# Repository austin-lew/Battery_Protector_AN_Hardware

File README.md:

# Battery_Protector_AN_Hardware

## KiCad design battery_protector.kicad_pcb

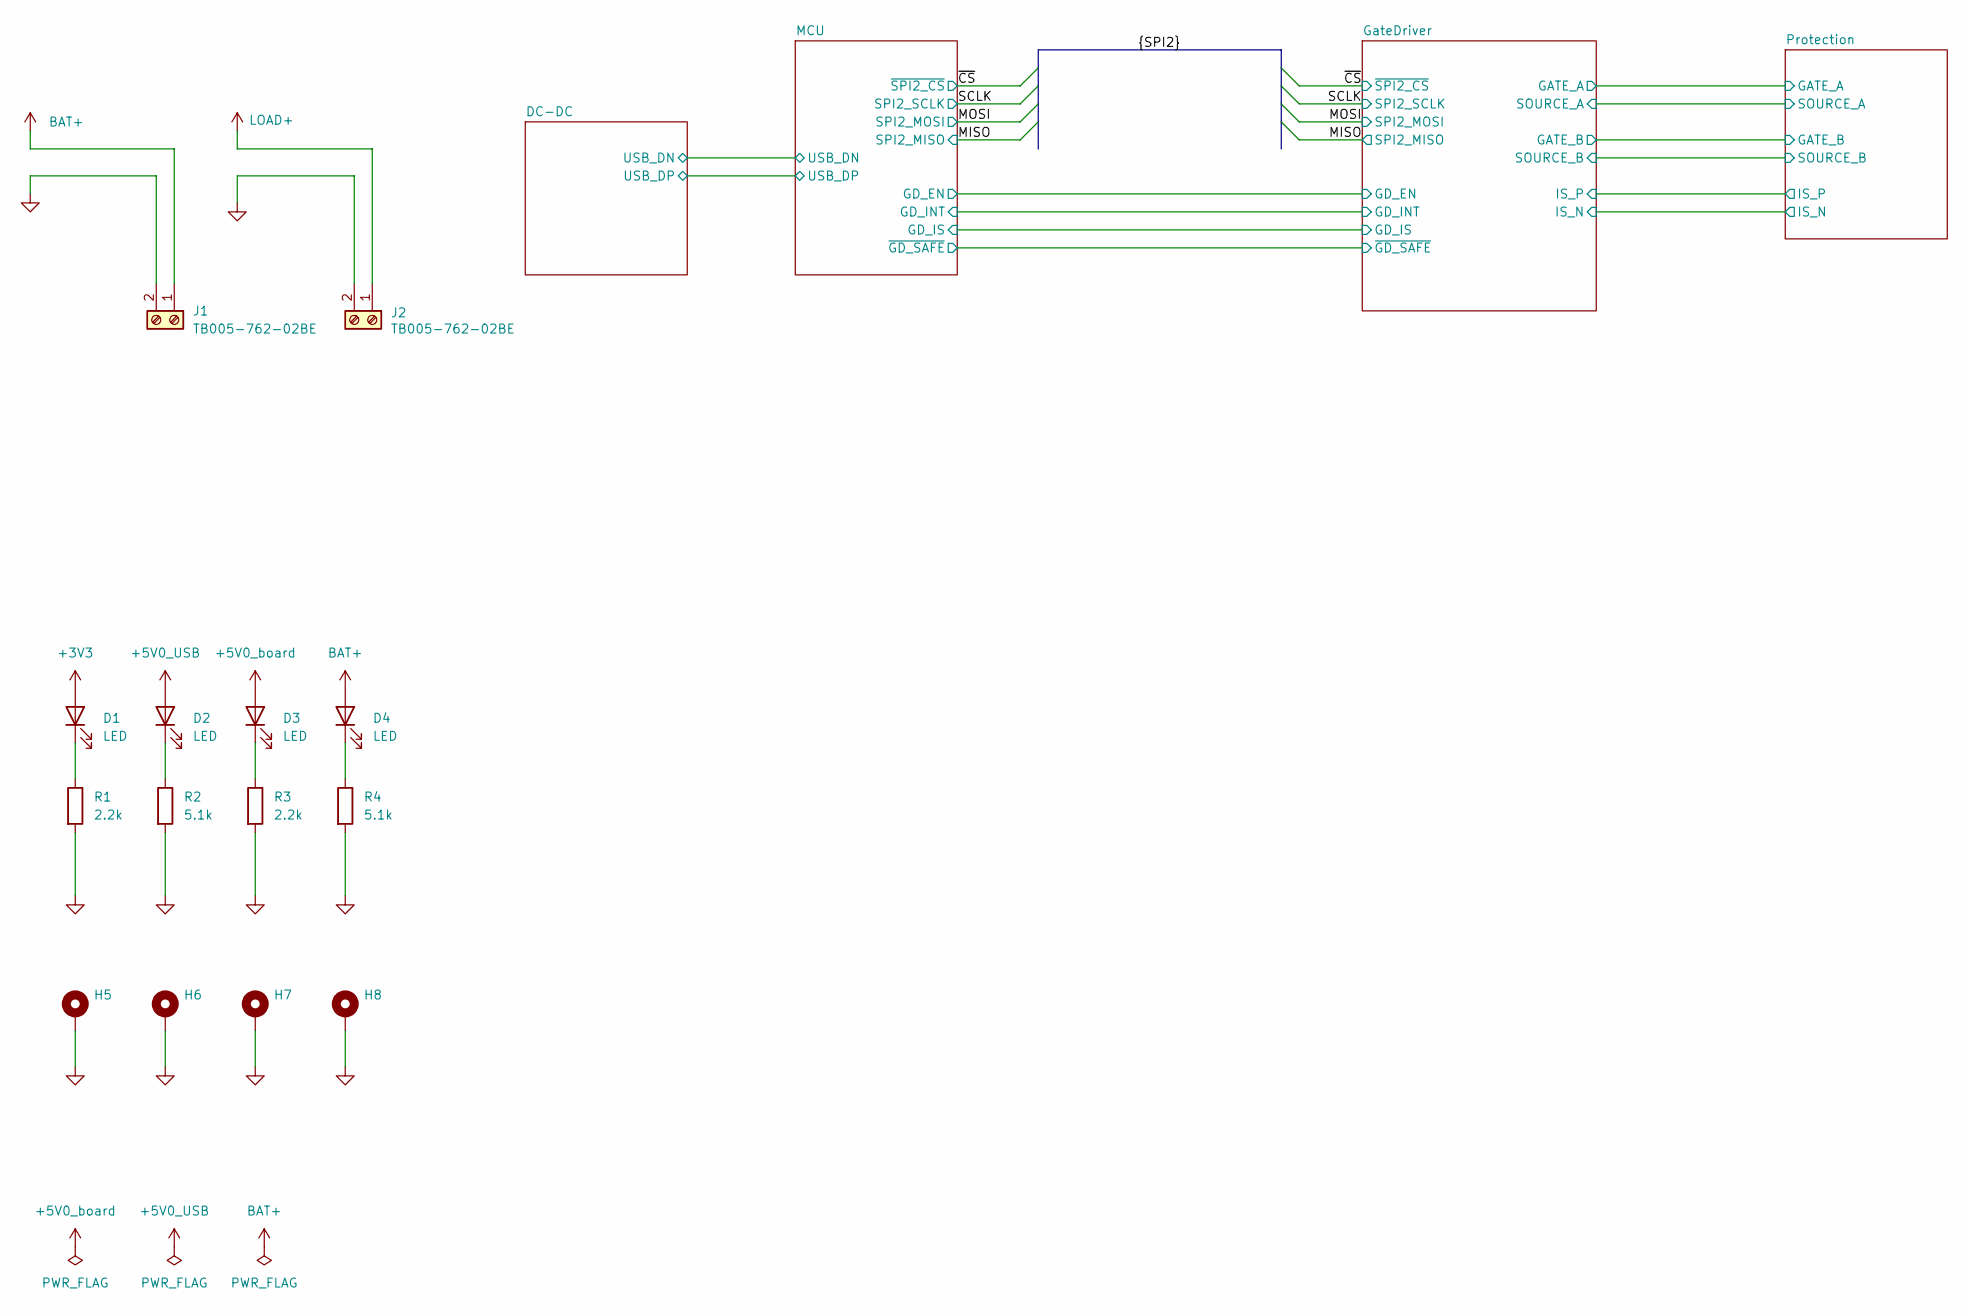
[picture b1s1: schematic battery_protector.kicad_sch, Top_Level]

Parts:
D1, D2, D3, D4: LED; LED_0603_1608Metric; Manufacturer_Part_Number LTST-C190GKT
H5, H6, H7, H8: MountingHole_Pad; MountingHole_3.2mm_M3_Pad_TopBottom
J1, J2: TB005-762-02BE; CUI_TB005-762-02BE; Manufacturer_Part_Number TB005-762-02BE
R1, R3: 2.2k; R_0603_1608Metric; Manufacturer_Part_Number RC0603FR-072K2L
R2, R4: 5.1k; R_0603_1608Metric; Manufacturer_Part_Number RC0603FR-075K1L

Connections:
+3V3: D1.2 (A); also elsewhere on the board
+5V0_USB: D2.2 (A); also elsewhere on the board
+5V0_board: D3.2 (A); also elsewhere on the board
BAT+: D4.2 (A), J1.1; also elsewhere on the board
unnamed: D1.1 (K), R1.1
unnamed: D2.1 (K), R2.1
unnamed: D3.1 (K), R3.1
unnamed: D4.1 (K), R4.1

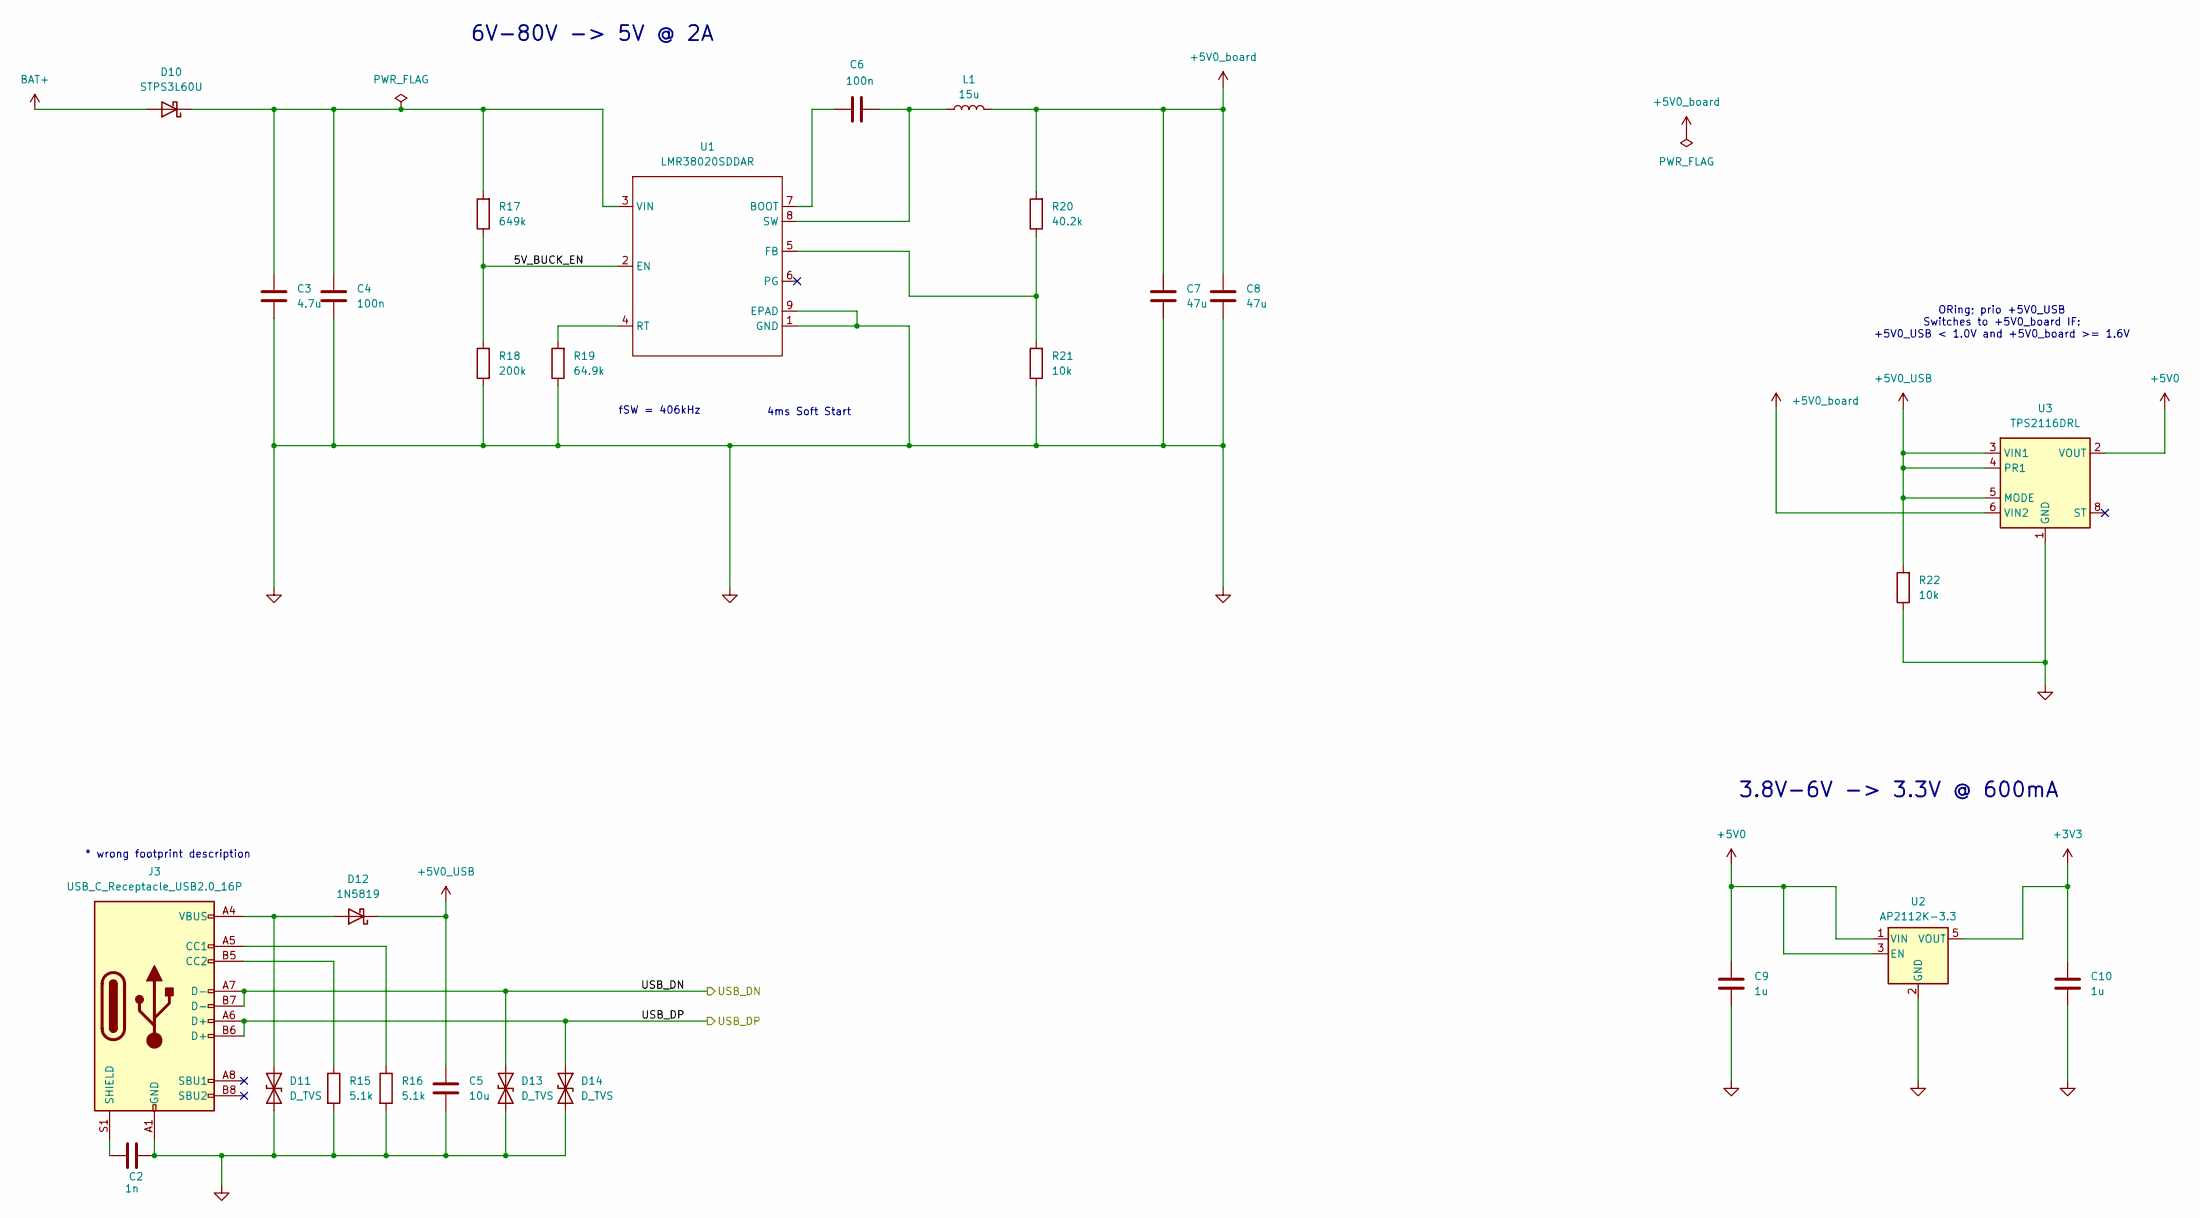
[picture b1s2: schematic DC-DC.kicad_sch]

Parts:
C2: 1n; C_0603_1608Metric; Manufacturer_Part_Number C0603C102K5RACTU
C3: 4.7u; C_1206_3216Metric; Manufacturer_Part_Number GRM31CC72A475KE11L
C4, C6: 100n; C_0603_1608Metric; Manufacturer_Part_Number CL10B104KC8NNNC
C5: 10u; C_0603_1608Metric; Manufacturer_Part_Number LMK107BBJ106MALT
C7, C8: 47u; C_0603_1608Metric; Manufacturer_Part_Number GRM188R60J476ME15D
C9, C10: 1u; C_0603_1608Metric; Manufacturer_Part_Number TMK107B7105KA-T
D10: STPS3L60U; Manufacturer_Part_Number STPS3L60U
D11, D13, D14: D_TVS; D_0402_1005Metric; Manufacturer_Part_Number D5V0H1B2LP-7B
D12: 1N5819; 1N5819HW-7-F; Manufacturer_Part_Number 1N5819HW-7-F
J3: USB_C_Receptacle_USB2.0_16P; USB_C_Receptacle_GCT_USB4105-xx-A_16P_TopMnt_Horizontal; Manufacturer_Part_Number USB4105-GF-A
L1: 15u; L_Bourns_SRR1208_12.7x12.7mm; Manufacturer_Part_Number SRR1208-150ML
R15, R16: 5.1k; R_0603_1608Metric; Manufacturer_Part_Number RC0603FR-075K1L
R17: 649k; R_0603_1608Metric; Manufacturer_Part_Number RC0603FR-07649KL
R18: 200k; R_0603_1608Metric; Manufacturer_Part_Number RC0603FR-07200KL
R19: 64.9k; R_0603_1608Metric; Manufacturer_Part_Number RC0603FR-0764K9L
R20: 40.2k; R_0603_1608Metric; Manufacturer_Part_Number RC0603FR-1340K2L
R21, R22: 10k; R_0603_1608Metric; Manufacturer_Part_Number RC0603JR-0710KL
U1: LMR38020SDDAR; Texas_R-PDSO-G8_EP2.95x4.9mm_Mask2.4x3.1mm; Manufacturer_Part_Number LMR38020SDDAR
U2: AP2112K-3.3; SOT-23-5; Manufacturer_Part_Number AP2112K-3.3TRG1
U3: TPS2116DRL; SOT-583-8; Manufacturer_Part_Number TPS2116DRLR

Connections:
+3V3: C10.1, U2.5 (VOUT); also elsewhere on the board
+5V0: C9.1, U2.1 (VIN), U2.3 (EN), U3.2 (VOUT), U3.7 (VOUT); also elsewhere on the board
+5V0_USB: C5.2, D12.1 (K), R22.2, U3.3 (VIN1), U3.4 (PR1), U3.5 (MODE); also elsewhere on the board
+5V0_board: C7.1, C8.1, L1.2, R20.2, U3.6 (VIN2); also elsewhere on the board
/DC-DC/5V_BUCK_EN: R17.1, R18.2, U1.2 (EN)
/DC-DC/USB_DN: D13.1 (A1), J3.A7 (D-), J3.B7 (D-); also elsewhere on the board
/DC-DC/USB_DP: D14.1 (A1), J3.A6 (D+), J3.B6 (D+); also elsewhere on the board
BAT+: D10.2 (A); also elsewhere on the board
unnamed: C3.1, C4.1, D10.1 (K), R17.2, U1.3 (VIN)
unnamed: D11.1 (A1), D12.2 (A), J3.A4 (VBUS), J3.A9 (VBUS), J3.B4 (VBUS), J3.B9 (VBUS)
unnamed: J3.A5 (CC1), R16.1
unnamed: J3.B5 (CC2), R15.1
unnamed: C2.1, J3.S1 (SHIELD)
unnamed: C6.2, U1.7 (BOOT)
unnamed: R20.1, R21.2, U1.5 (FB)
unnamed: R19.2, U1.4 (RT)
unnamed: C6.1, L1.1, U1.8 (SW)

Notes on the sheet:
3.8V-6V -> 3.3V @ 600mA
ORing; prio +5V0_USB Switches to +5V0_board IF: +5V0_USB < 1.0V and +5V0_board >= 1.6V
fSW = 406kHz
4ms Soft Start
6V-80V -> 5V @ 2A
* wrong footprint description

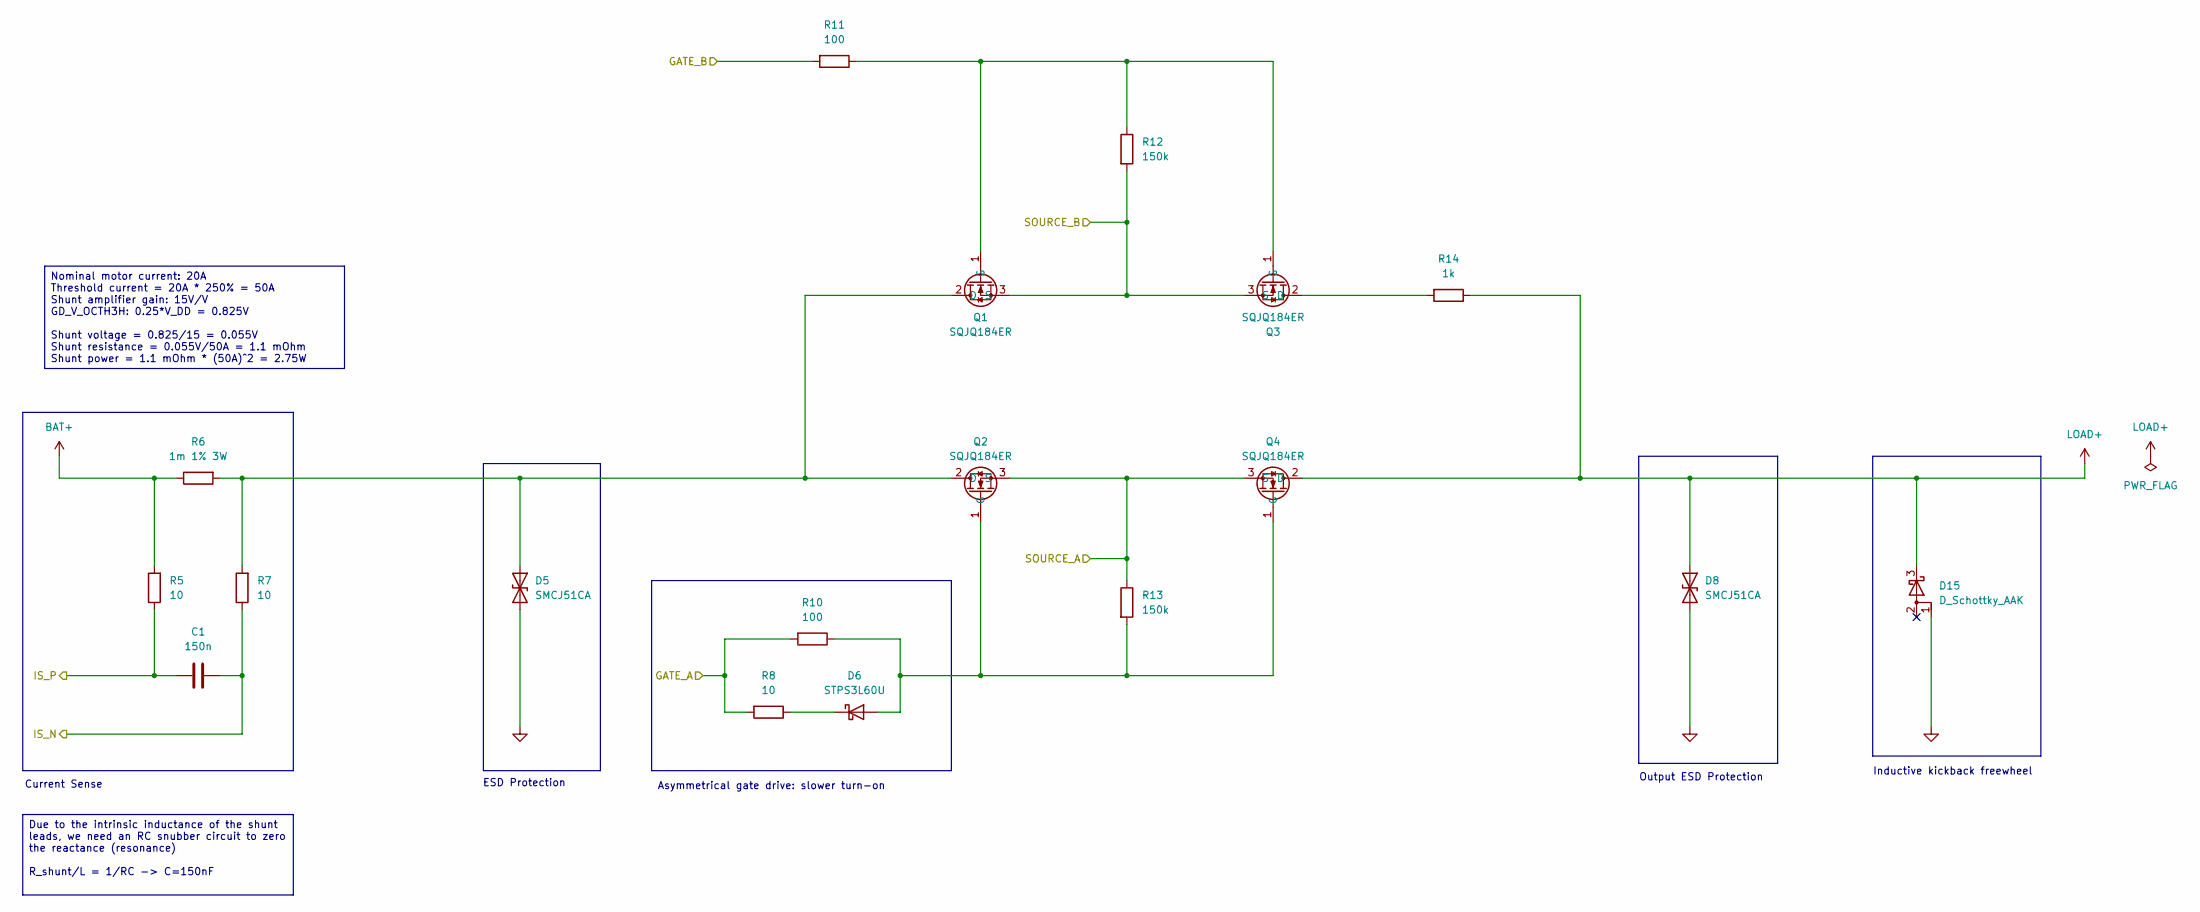
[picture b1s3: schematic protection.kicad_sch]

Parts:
C1: 150n; C_0603_1608Metric; Manufacturer_Part_Number CL10B154KO8NNNC
D5, D8: SMCJ51CA; D_SMC; Manufacturer_Part_Number SMCJ51CA
D6: STPS3L60U; Manufacturer_Part_Number STPS3L60U
D15: D_Schottky_AAK; VB30100S-E38W; Manufacturer_Part_Number VB30100S-E3/8W
Q1, Q2, Q3, Q4: SQJQ184ER; Manufacturer_Part_Number SQJQ184ER-T1_GE3
R5, R7, R8: 10; R_0603_1608Metric; Manufacturer_Part_Number RC0603FR-0710RL
R6: 1m 1% 3W; WSK12161L000FEA; Manufacturer_Part_Number WSK12161L000FEA
R10, R11: 100; R_0603_1608Metric; Manufacturer_Part_Number RC0603FR-0710RL
R12, R13: 150k; R_0603_1608Metric; Manufacturer_Part_Number AC0603FR-07150KL
R14: 1k; R_1206_3216Metric; Manufacturer_Part_Number HRG3216P-1001-D-T1

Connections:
/GateDriver/GATE_A: R8.2, R10.2; also elsewhere on the board
/GateDriver/GATE_B: R11.2; also elsewhere on the board
/GateDriver/IS_N: C1.1, R7.1; also elsewhere on the board
/GateDriver/IS_P: C1.2, R5.1; also elsewhere on the board
/GateDriver/SOURCE_A: Q2.3 (S), Q4.3 (S), R13.1; also elsewhere on the board
/GateDriver/SOURCE_B: Q1.3 (S), Q3.3 (S), R12.2; also elsewhere on the board
BAT+: R5.2, R6.1; also elsewhere on the board
unnamed: D5.1 (A1), Q1.2 (D), Q2.2 (D), R6.2, R7.2
unnamed: D6.2 (A), Q2.1 (G), Q4.1 (G), R10.1, R13.2
unnamed: D6.1 (K), R8.1
unnamed: Q1.1 (G), Q3.1 (G), R11.1, R12.1
unnamed: Q3.2 (D), R14.2

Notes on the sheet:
Output ESD Protection
Asymmetrical gate drive: slower turn-on
Current Sense
Inductive kickback freewheel
ESD Protection
Nominal motor current: 20A Threshold current = 20A * 250% = 50A Shunt amplifier gain: 15V/V GD_V_OCTH3H: 0.25*V_DD = 0.825V Shunt voltage = 0.825/15 = 0.055V Shunt resistance = 0.055V/50A = 1.1 mOhm Shunt power = 1.1 mOhm * (50A)^2 = 2.75W
Due to the intrinsic inductance of the shunt leads, we need an RC snubber circuit to zero the reactance (resonance) R_shunt/L = 1/RC -> C=150nF

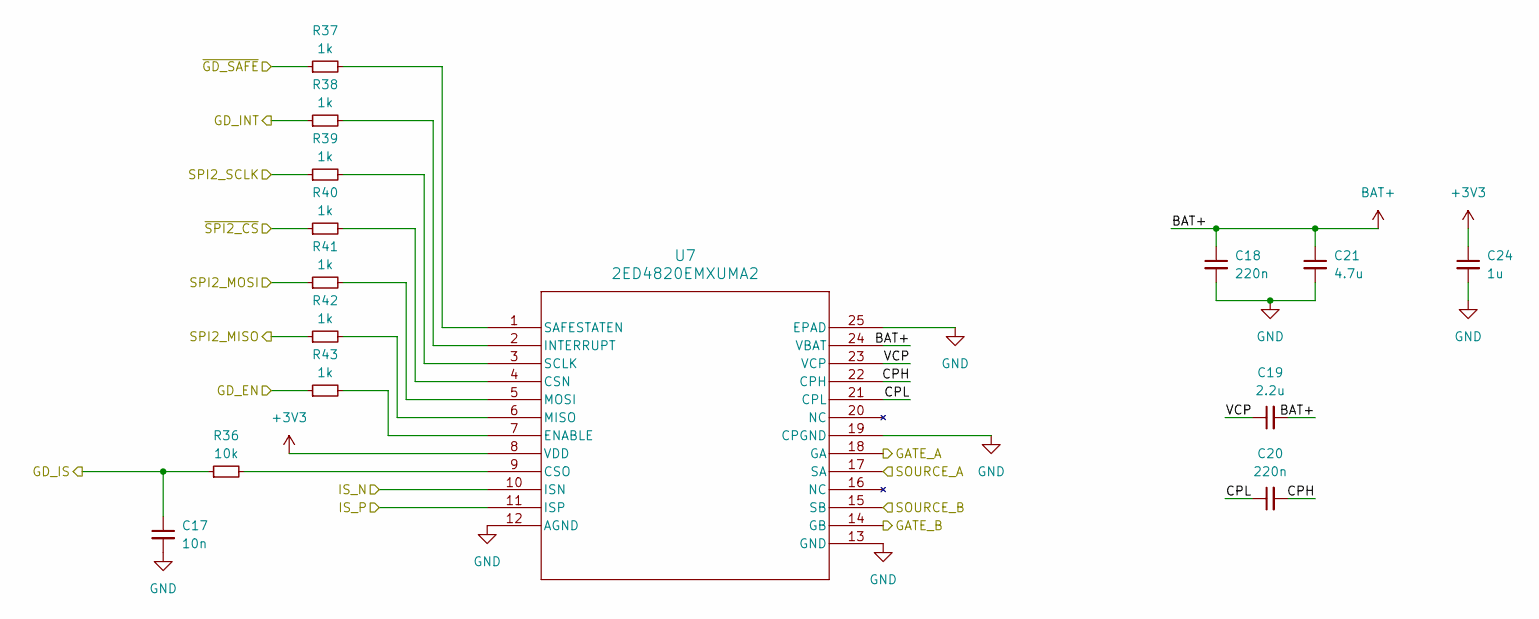
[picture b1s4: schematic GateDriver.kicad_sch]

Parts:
C17: 10n; C_0603_1608Metric; Manufacturer_Part_Number GCM188R72A103KA37D
C18, C20: 220n; C_1206_3216Metric; Manufacturer_Part_Number C3216X7R2A224K115AA
C19: 2.2u; C_1206_3216Metric; Manufacturer_Part_Number CL31B225KCHSNNE
C21: 4.7u; C_1206_3216Metric; Manufacturer_Part_Number GRM31CC72A475KE11L
C24: 1u; C_0603_1608Metric; Manufacturer_Part_Number TMK107B7105KA-T
R36: 10k; R_0603_1608Metric; Manufacturer_Part_Number RC0603JR-0710KL
R37, R38, R39, R40, R41, R42, R43: 1k; R_0603_1608Metric; Manufacturer_Part_Number RC0603FR-071KL
U7: 2ED4820EMXUMA2; 2ed4820emxuma2; Manufacturer_Part_Number 2ED4820EMXUMA2

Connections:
+3V3: C24.1, U7.8 (VDD); also elsewhere on the board
/GateDriver/CPH: C20.2, U7.22 (CPH)
/GateDriver/CPL: C20.1, U7.21 (CPL)
/GateDriver/GATE_A: U7.18 (GA); also elsewhere on the board
/GateDriver/GATE_B: U7.14 (GB); also elsewhere on the board
/GateDriver/IS_N: U7.10 (ISN); also elsewhere on the board
/GateDriver/IS_P: U7.11 (ISP); also elsewhere on the board
/GateDriver/SOURCE_A: U7.17 (SA); also elsewhere on the board
/GateDriver/SOURCE_B: U7.15 (SB); also elsewhere on the board
/GateDriver/VCP: C19.1, U7.23 (VCP)
/MCU/GD_EN: R43.1; also elsewhere on the board
/MCU/GD_INT: R38.1; also elsewhere on the board
/MCU/GD_IS: C17.1, R36.1; also elsewhere on the board
/MCU/~GD_SAFE: R37.1; also elsewhere on the board
/MISO: R42.1; also elsewhere on the board
/MOSI: R41.1; also elsewhere on the board
/SCLK: R39.1; also elsewhere on the board
/~CS: R40.1; also elsewhere on the board
BAT+: C18.1, C19.2, C21.1, U7.24 (VBAT); also elsewhere on the board
unnamed: R40.2, U7.4 (CSN)
unnamed: R36.2, U7.9 (CSO)
unnamed: R43.2, U7.7 (ENABLE)
unnamed: R38.2, U7.2 (INTERRUPT)
unnamed: R42.2, U7.6 (MISO)
unnamed: R41.2, U7.5 (MOSI)
unnamed: R37.2, U7.1 (SAFESTATEN)
unnamed: R39.2, U7.3 (SCLK)

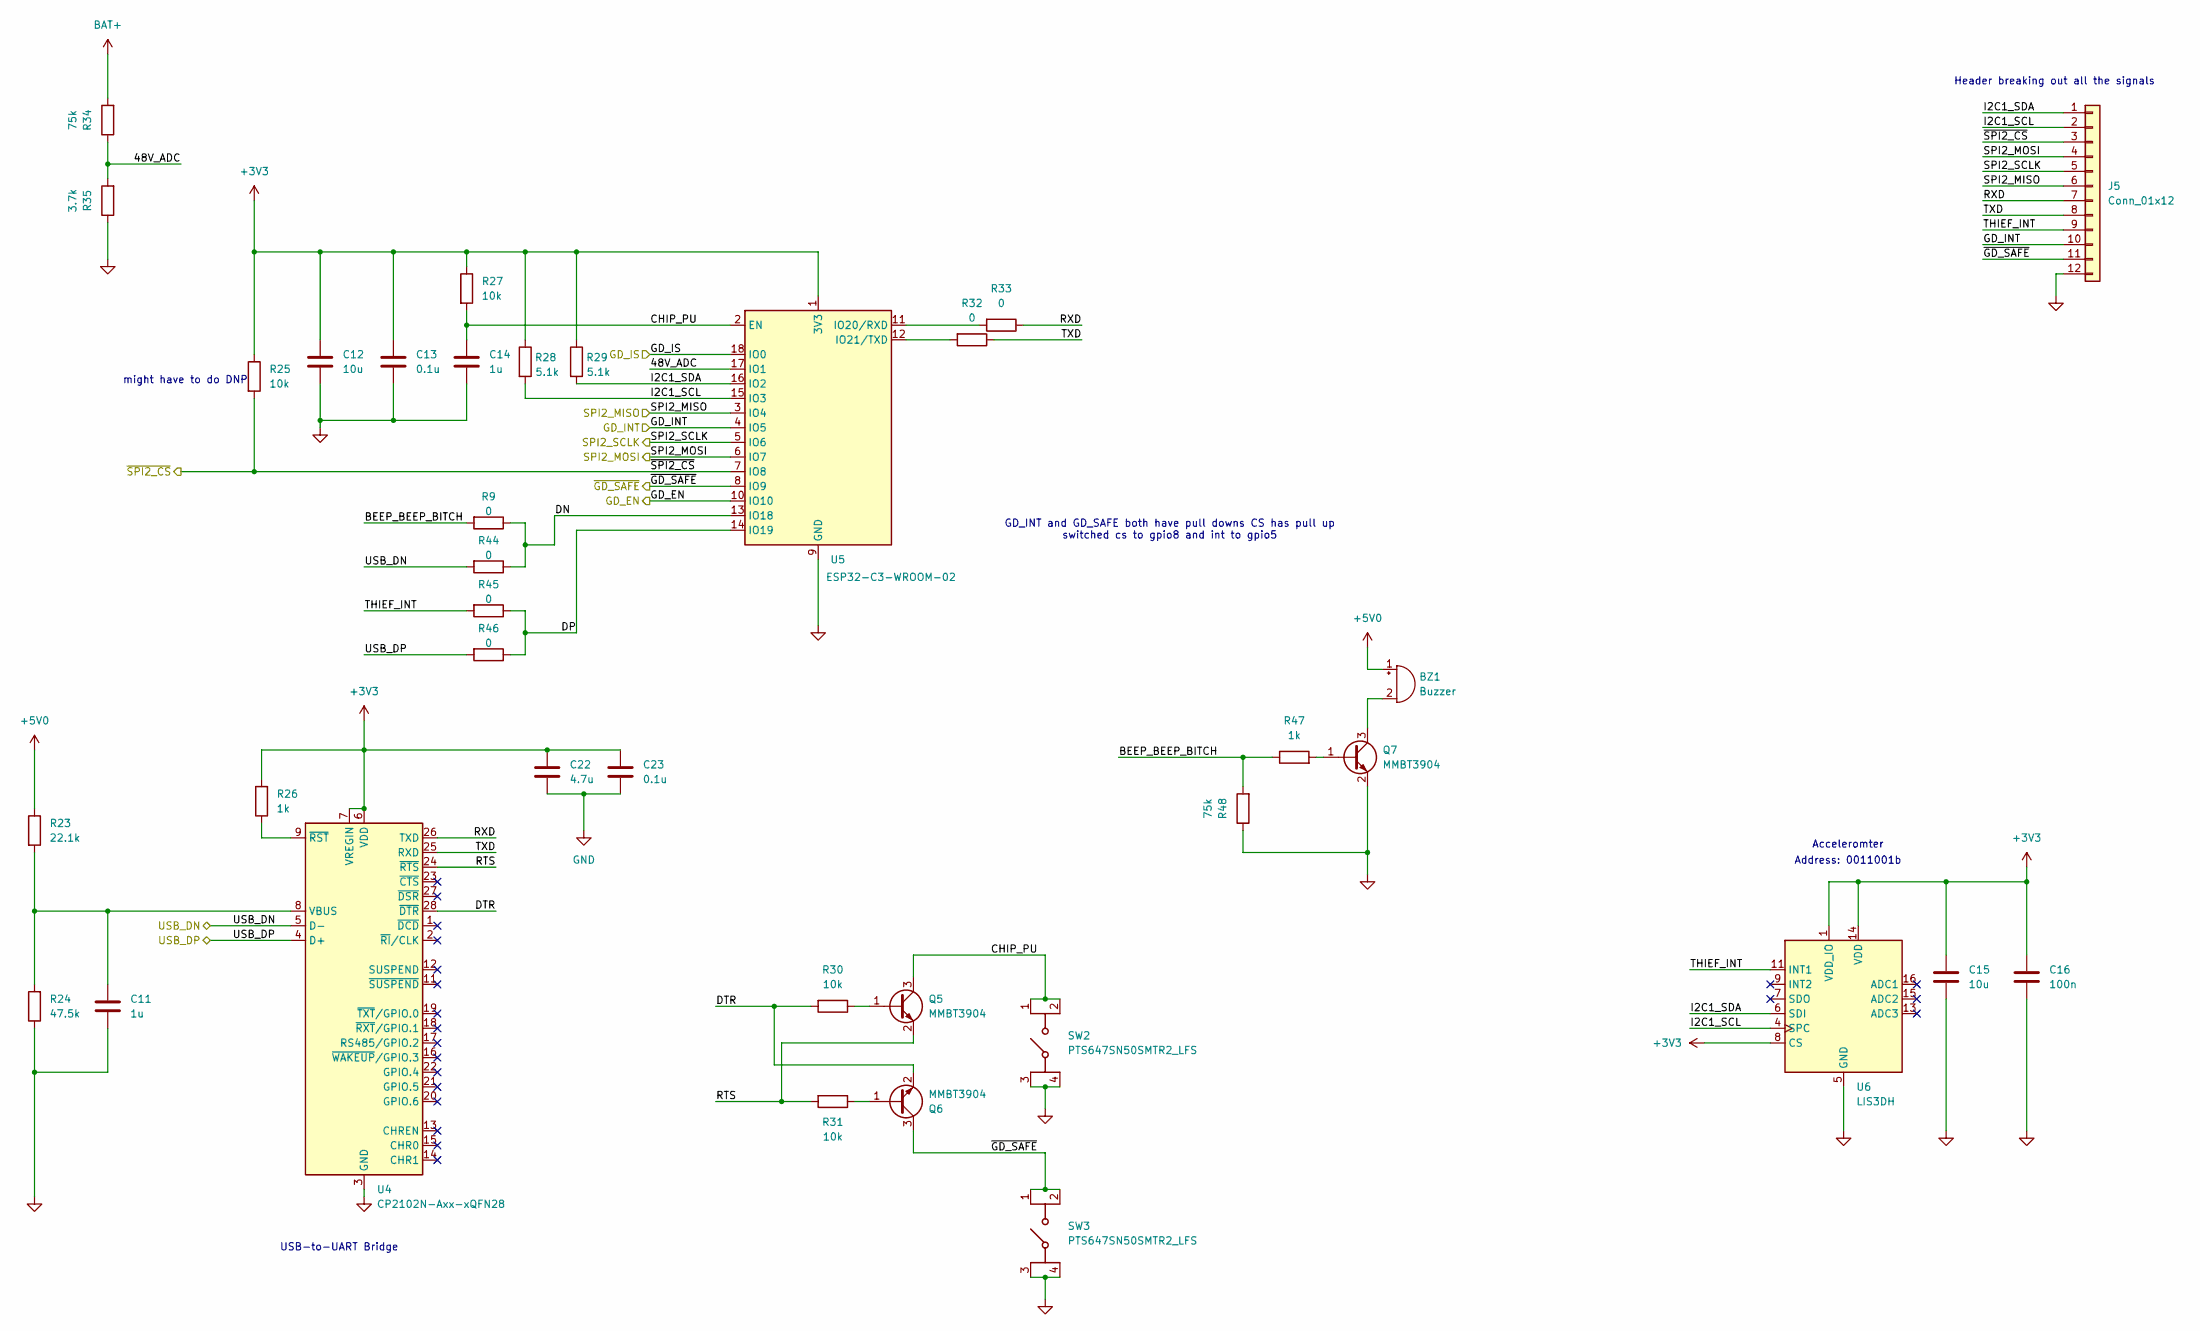
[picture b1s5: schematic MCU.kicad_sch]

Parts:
BZ1: Buzzer; MagneticBuzzer_CT_1205C_SMT_TR
C11, C14: 1u; C_0603_1608Metric; Manufacturer_Part_Number TMK107B7105KA-T
C12, C15: 10u; C_0603_1608Metric; Manufacturer_Part_Number LMK107BBJ106MALT
C13, C23: 0.1u; C_0603_1608Metric; Manufacturer_Part_Number CC0603KRX7R7BB104
C16: 100n; C_0603_1608Metric; Manufacturer_Part_Number CL10B104KC8NNNC
C22: 4.7u; C_0603_1608Metric; Manufacturer_Part_Number CL10A475KP8NNNC
J5: Conn_01x12; PinHeader_1x12_P2.54mm_Vertical
Q5, Q6, Q7: MMBT3904; SOT-23; Manufacturer_Part_Number MMBT3904 RFG
R9, R32, R33, R44, R45, R46: 0; R_0603_1608Metric
R23: 22.1k; R_0603_1608Metric; Manufacturer_Part_Number RC0603FR-0722K1L
R24: 47.5k; R_0603_1608Metric; Manufacturer_Part_Number RC0603FR-0747K5L
R25, R27, R30, R31: 10k; R_0603_1608Metric; Manufacturer_Part_Number RC0603JR-0710KL
R26, R47: 1k; R_0603_1608Metric; Manufacturer_Part_Number RC0603FR-071KL
R28, R29: 5.1k; R_0603_1608Metric; Manufacturer_Part_Number RC0603FR-075K1L
R34, R48: 75k; R_0603_1608Metric; Manufacturer_Part_Number AC0603FR-0775KL
R35: 3.7k; R_0603_1608Metric; Manufacturer_Part_Number RN73H1JTTD3701B25
SW2, SW3: PTS647SN50SMTR2_LFS; PTS647SK50SMTR2LFS; Manufacturer_Part_Number PTS647SN50SMTR2 LFS
U4: CP2102N-Axx-xQFN28; QFN-28-1EP_5x5mm_P0.5mm_EP3.35x3.35mm; Manufacturer_Part_Number CP2102N-A02-GQFN28
U5: ESP32-C3-WROOM-02; ESP32-C3-WROOM; Manufacturer_Part_Number ESP32-C3-WROOM-02-H4
U6: LIS3DH; LGA-16_3x3mm_P0.5mm_LayoutBorder3x5y; Manufacturer_Part_Number LIS3DH

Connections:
+3V3: C12.1, C13.1, C15.1, C16.1, C22.1, C23.1, R25.1, R26.2, R27.1, R28.1, R29.1, U4.6 (VDD), U4.7 (VREGIN), U5.1 (3V3), U6.1 (VDD_IO), U6.8 (CS), U6.14 (VDD); also elsewhere on the board
+5V0: BZ1.1 (+), R23.1; also elsewhere on the board
/DC-DC/USB_DN: R44.2, U4.5 (D-); also elsewhere on the board
/DC-DC/USB_DP: R46.2, U4.4 (D+); also elsewhere on the board
/MCU/48V_ADC: R34.1, R35.2, U5.17 (IO1)
/MCU/BEEP_BEEP_BITCH: R9.2, R47.1, R48.2
/MCU/CHIP_PU: C14.1, Q5.3 (C), R27.2, SW2.1 (NO_1), SW2.2 (NO_2), U5.2 (EN)
/MCU/DN: R9.1, R44.1, U5.13 (IO18)
/MCU/DP: R45.1, R46.1, U5.14 (IO19)
/MCU/DTR: Q6.2 (E), R30.2, U4.28 (~DTR)
/MCU/GD_EN: U5.10 (IO10); also elsewhere on the board
/MCU/GD_INT: J5.10, U5.4 (IO5); also elsewhere on the board
/MCU/GD_IS: U5.18 (IO0); also elsewhere on the board
/MCU/I2C1_SCL: J5.2, R28.2, U5.15 (IO3), U6.4 (SPC)
/MCU/I2C1_SDA: J5.1, R29.2, U5.16 (IO2), U6.6 (SDI)
/MCU/RTS: Q5.2 (E), R31.2, U4.24 (~RTS)
/MCU/RXD: J5.7, R33.1, U4.26 (TXD)
/MCU/THIEF_INT: J5.9, R45.2, U6.11 (INT1)
/MCU/TXD: J5.8, R32.1, U4.25 (RXD)
/MCU/~GD_SAFE: J5.11, Q6.3 (C), SW3.1 (NO_1), SW3.2 (NO_2), U5.8 (IO9); also elsewhere on the board
/MISO: J5.6, U5.3 (IO4); also elsewhere on the board
/MOSI: J5.4, U5.6 (IO7); also elsewhere on the board
/SCLK: J5.5, U5.5 (IO6); also elsewhere on the board
/~CS: J5.3, R25.2, U5.7 (IO8); also elsewhere on the board
BAT+: R34.2; also elsewhere on the board
unnamed: BZ1.2 (-), Q7.3 (C)
unnamed: Q5.1 (B), R30.1
unnamed: Q6.1 (B), R31.1
unnamed: Q7.1 (B), R47.2
unnamed: C11.1, R23.2, R24.2, U4.8 (VBUS)
unnamed: R26.1, U4.9 (~RST)
unnamed: R33.2, U5.11 (IO20/RXD)
unnamed: R32.2, U5.12 (IO21/TXD)

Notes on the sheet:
Acceleromter
might have to do DNP
Address: 0011001b
GD_INT and GD_SAFE both have pull downs CS has pull up switched cs to gpio8 and int to gpio5
USB-to-UART Bridge
Header breaking out all the signals

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
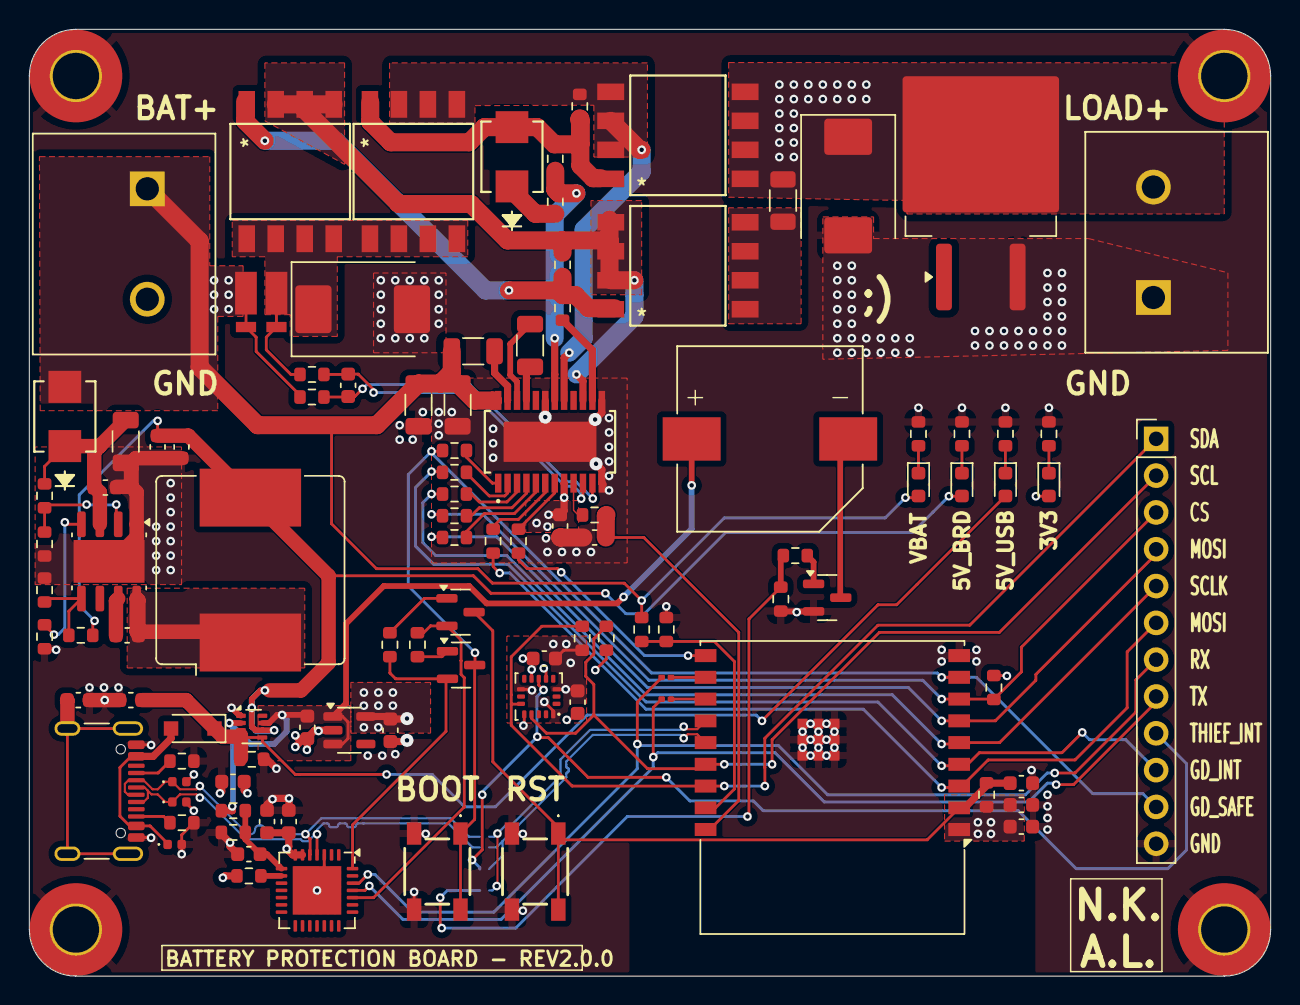
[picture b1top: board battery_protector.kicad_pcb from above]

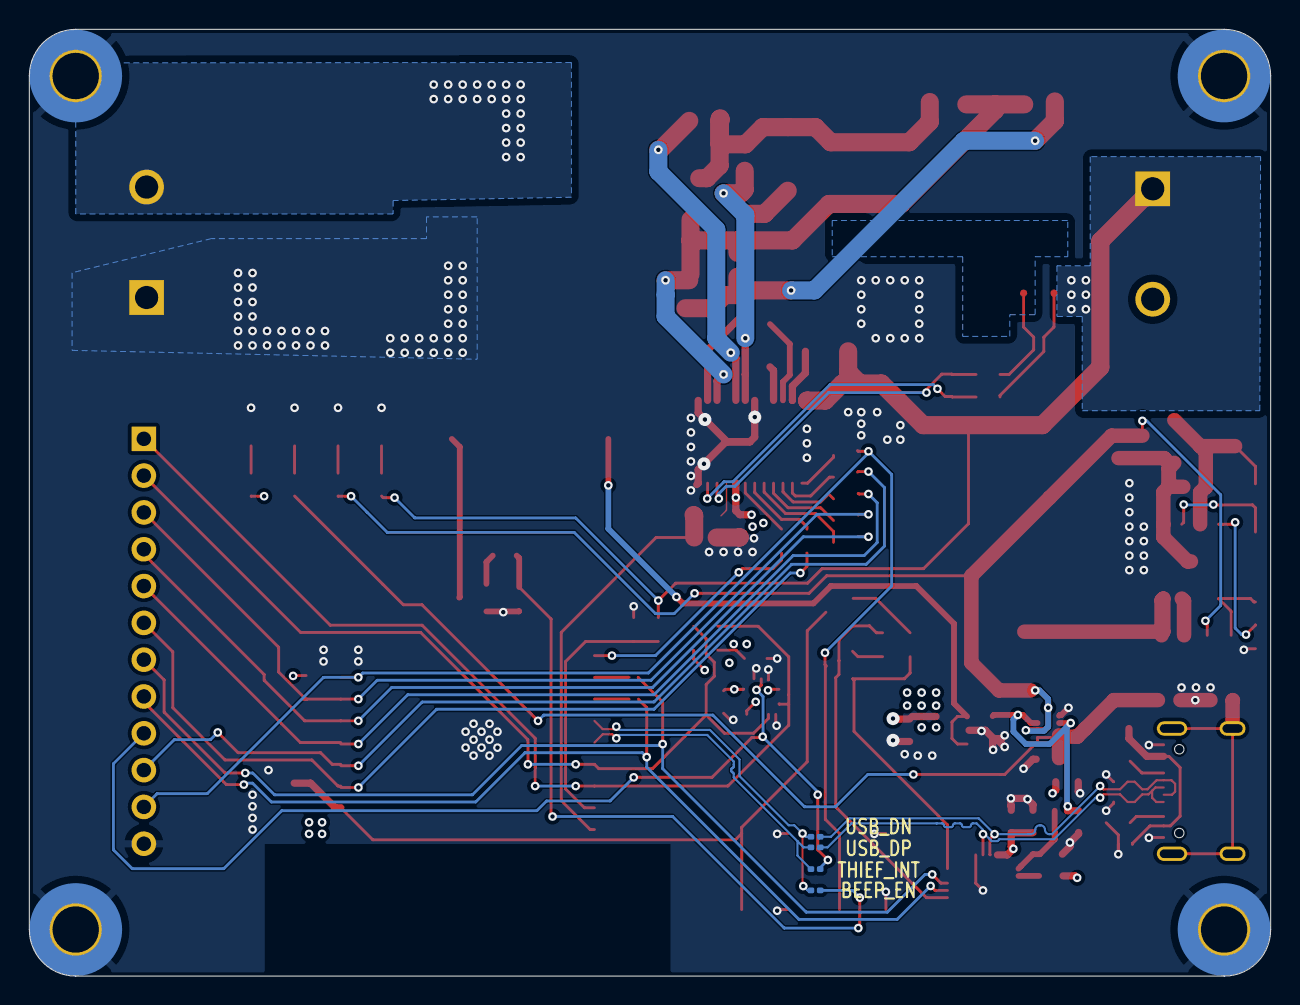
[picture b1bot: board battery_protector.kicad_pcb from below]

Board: 4 copper layers, 85.7 x 65.3 mm, 112 parts (4 on the bottom side), 73 nets.

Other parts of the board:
C25: 0.1u; C_0603_1608Metric

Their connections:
+3V3: C25.1; also elsewhere on the board

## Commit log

2025-03-28 setup project skeleton
2025-04-07 add rev1 images
2025-04-23 Addded new sheets for Protection, usb-pd, mcu, gatedriver, and dc-dc
2025-05-15 add gate driver
2025-05-15 Add gate driver (#1)
    * Addded new sheets for Protection, usb-pd, mcu, gatedriver, and dc-dc
    * add gate driver
    ---------
2025-06-19 add digikey symbols
2025-06-26 Worked on the MCU page and the DC-DC page. Will still need to change a few things and add the buzzer and piezo stuff
2025-06-26 Worked on the MCU page and the DC-DC page. Will still need to change a few things and add the buzzer and piezo stuff (#3)
2025-07-02 finish protection sheet
2025-07-06 jul 2 design review
2025-07-10 Added footprints to resistors and capacitors, and fixed the mosfets wiring issue
2025-07-10 Added footprints to resistors and capacitors, and fixed the mosfets wiring issue (#4)
    Jul9th push. Added footprints to resistors and capacitors, and fixed the mosfets wiring issue
2025-07-10 add pics from testing
2025-07-20 finish schematic
2025-07-20 setup layout rules
2025-07-27 first pass layout
2025-07-28 Updated pcb rules and started the rough routing of protection circuitry
2025-07-28 Updated pcb rules and started the rough routing of protection circuitry (#5)
2025-08-11 Did some more routing
2025-08-11 Nima/changes aug 11 (#6)
    * Updated pcb rules and started the rough routing of protection circuitry
    * Did some more routing
2025-08-12 route dc-dc
2025-08-15 Routed Gate Driver, will have to move all components to top layer for simplicity and move the switching reg farther away from the mcu
2025-08-16 More routing, changed the footprints of some caps.
2025-08-16 Nima/aug 16 (#7)
    * Routed Gate Driver, will have to move all components to top layer for simplicity and move the switching reg farther away from the mcu
    * More routing, changed the footprints of some caps.
2025-08-17 Finished Routing and ran DRC. Will need final review of schematics and layout with Austin. Will also need to update BOM.
2025-08-17 add manufacturer, mpn, and package to bom
2025-08-19 Caught some issues and made final changes for manufacturing
2025-08-19 Caught some issues and made final changes for manufacturing (#9)
    Caught some issues and made final changes for manufacturing including correcting the imu and J2 footprints, updating the clearance rules we imported from pcbway (.09mm->0.1mm), and the addition of st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
2025-09-01 create new .pos file with fixed footprints
